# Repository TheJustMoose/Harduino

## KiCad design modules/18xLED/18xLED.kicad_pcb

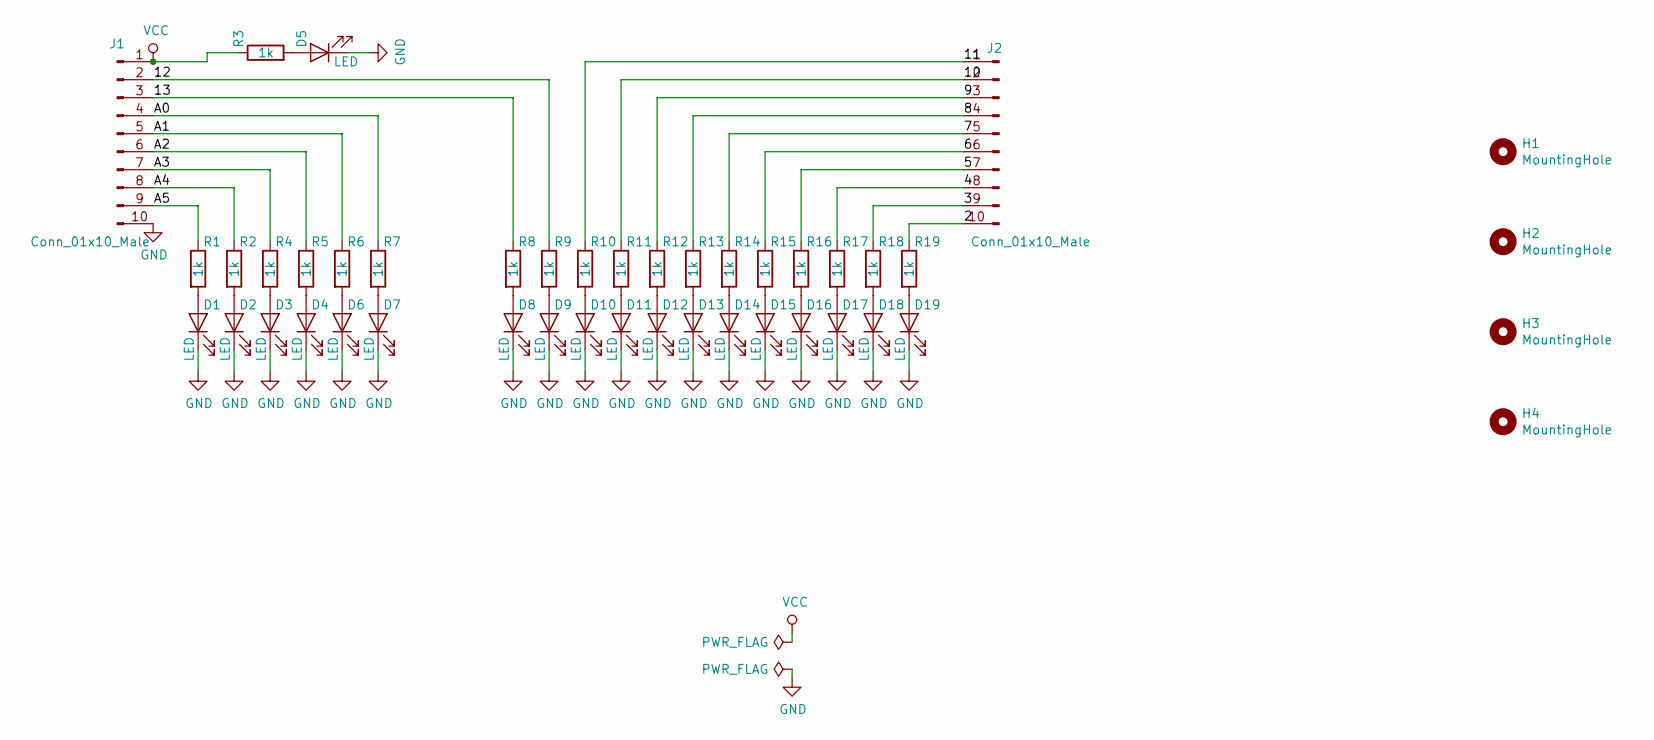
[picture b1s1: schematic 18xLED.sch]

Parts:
D1, D2, D3, D4, D5, D6, D7, D8, D9, D10, D11, D12, D13, D14, D15, D16, D17, D18, D19: LED; LED_0805_2012Metric_Pad1.15x1.40mm_HandSolder
H1, H2, H3, H4: MountingHole; MountingHole_3.2mm_M3
J1, J2: Conn_01x10_Male; PinSocket_1x10_P2.54mm_Vertical
R1, R2, R3, R4, R5, R6, R7, R8, R9, R10, R11, R12, R13, R14, R15, R16, R17, R18, R19: 1k; R_0805_2012Metric_Pad1.15x1.40mm_HandSolder

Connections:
/2: J2.10, R19.1
/3: J2.9, R18.1
/4: J2.8, R17.1
/5: J2.7, R16.1
/6: J2.6, R15.1
/7: J2.5, R14.1
/8: J2.4, R13.1
/9: J2.3, R12.1
/10: J2.2, R11.1
/11: J2.1, R10.1
/12: J1.2, R9.1
/13: J1.3, R8.1
/A0: J1.4, R7.1
/A1: J1.5, R6.1
/A2: J1.6, R5.1
/A3: J1.7, R4.1
/A4: J1.8, R2.1
/A5: J1.9, R1.1
GND: D1.1 (K), D2.1 (K), D3.1 (K), D4.1 (K), D5.1 (K), D6.1 (K), D7.1 (K), D8.1 (K), D9.1 (K), D10.1 (K), D11.1 (K), D12.1 (K), D13.1 (K), D14.1 (K), D15.1 (K), D16.1 (K), D17.1 (K), D18.1 (K), D19.1 (K), J1.10
unnamed: D1.2 (A), R1.2
unnamed: D2.2 (A), R2.2
unnamed: D3.2 (A), R4.2
unnamed: D4.2 (A), R5.2
unnamed: D5.2 (A), R3.2
unnamed: D6.2 (A), R6.2
unnamed: D7.2 (A), R7.2
unnamed: D8.2 (A), R8.2
unnamed: D9.2 (A), R9.2
unnamed: D10.2 (A), R10.2
unnamed: D11.2 (A), R11.2
unnamed: D12.2 (A), R12.2
unnamed: D13.2 (A), R13.2
unnamed: D14.2 (A), R14.2
unnamed: D15.2 (A), R15.2
unnamed: D16.2 (A), R16.2
unnamed: D17.2 (A), R17.2
unnamed: D18.2 (A), R18.2
unnamed: D19.2 (A), R19.2
VCC: J1.1, R3.1

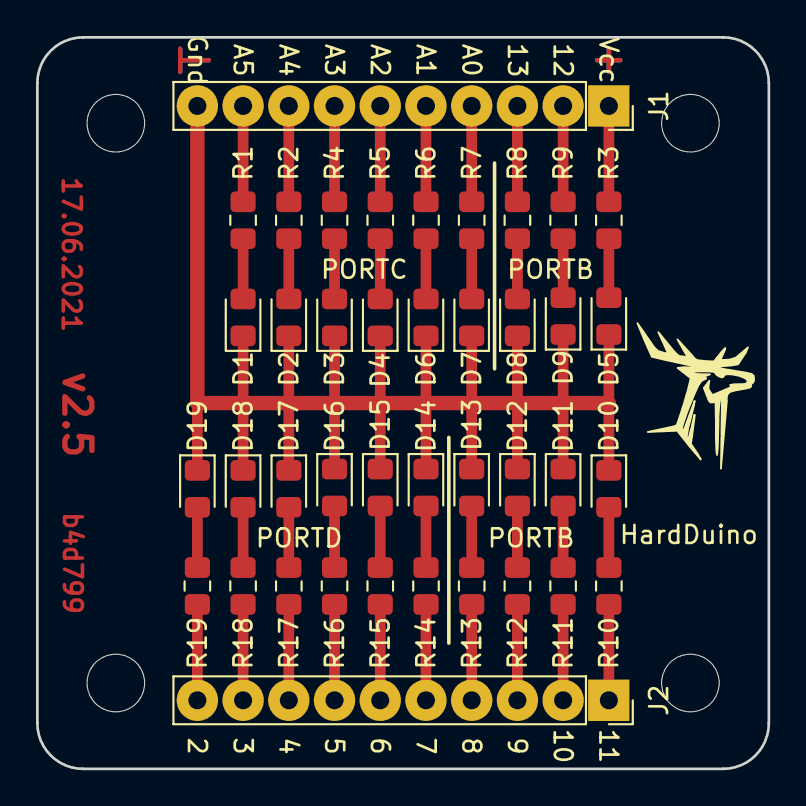
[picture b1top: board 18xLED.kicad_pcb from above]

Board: 2 copper layers, 40.6 x 40.6 mm, 44 parts (0 on the bottom side), 39 nets.

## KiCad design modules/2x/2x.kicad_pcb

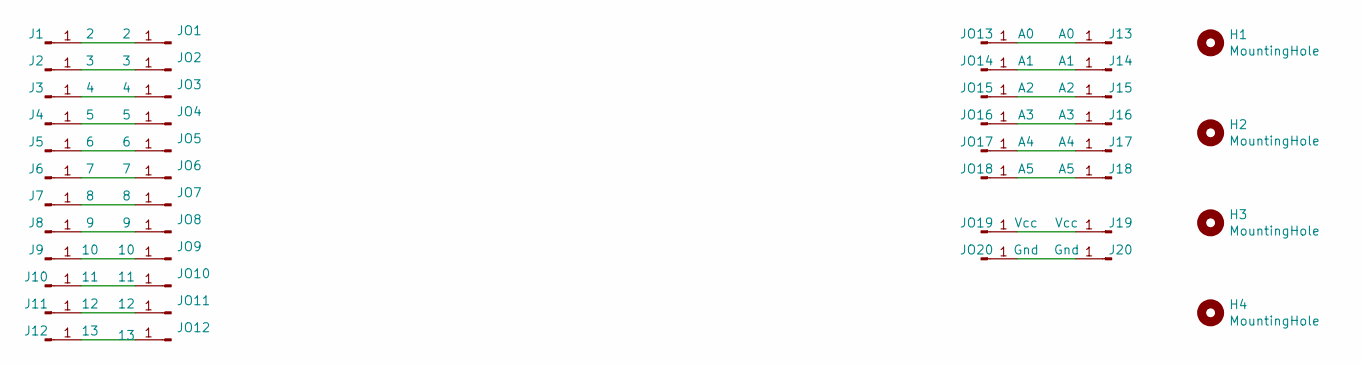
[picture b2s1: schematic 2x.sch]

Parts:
H1, H2, H3, H4: MountingHole; MountingHole_3.2mm_M3
J1: 2; PinHeader_1x01_P2.54mm_Vertical
J2: 3; PinHeader_1x01_P2.54mm_Vertical
J3: 4; PinHeader_1x01_P2.54mm_Vertical
J4: 5; PinHeader_1x01_P2.54mm_Vertical
J5: 6; PinHeader_1x01_P2.54mm_Vertical
J6: 7; PinHeader_1x01_P2.54mm_Vertical
J7: 8; PinHeader_1x01_P2.54mm_Vertical
J8: 9; PinHeader_1x01_P2.54mm_Vertical
J9: 10; PinHeader_1x01_P2.54mm_Vertical
J10: 11; PinHeader_1x01_P2.54mm_Vertical
J11: 12; PinHeader_1x01_P2.54mm_Vertical
J12: 13; PinHeader_1x01_P2.54mm_Vertical
J13: A0; PinHeader_1x01_P2.54mm_Vertical
J14: A1; PinHeader_1x01_P2.54mm_Vertical
J15: A2; PinHeader_1x01_P2.54mm_Vertical
J16: A3; PinHeader_1x01_P2.54mm_Vertical
J17: A4; PinHeader_1x01_P2.54mm_Vertical
J18: A5; PinHeader_1x01_P2.54mm_Vertical
J19: Vcc; PinHeader_1x01_P2.54mm_Vertical
J20: Gnd; PinHeader_1x01_P2.54mm_Vertical
JO1: 2; PinHeader_1x01_P2.54mm_Vertical
JO2: 3; PinHeader_1x01_P2.54mm_Vertical
JO3: 4; PinHeader_1x01_P2.54mm_Vertical
JO4: 5; PinHeader_1x01_P2.54mm_Vertical
JO5: 6; PinHeader_1x01_P2.54mm_Vertical
JO6: 7; PinHeader_1x01_P2.54mm_Vertical
JO7: 8; PinHeader_1x01_P2.54mm_Vertical
JO8: 9; PinHeader_1x01_P2.54mm_Vertical
JO9: 10; PinHeader_1x01_P2.54mm_Vertical
JO10: 11; PinHeader_1x01_P2.54mm_Vertical
JO11: 12; PinHeader_1x01_P2.54mm_Vertical
JO12: 13; PinHeader_1x01_P2.54mm_Vertical
JO13: A0; PinHeader_1x01_P2.54mm_Vertical
JO14: A1; PinHeader_1x01_P2.54mm_Vertical
JO15: A2; PinHeader_1x01_P2.54mm_Vertical
JO16: A3; PinHeader_1x01_P2.54mm_Vertical
JO17: A4; PinHeader_1x01_P2.54mm_Vertical
JO18: A5; PinHeader_1x01_P2.54mm_Vertical
JO19: Vcc; PinHeader_1x01_P2.54mm_Vertical
JO20: Gnd; PinHeader_1x01_P2.54mm_Vertical

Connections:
unnamed: J1.1, JO1.1
unnamed: J2.1, JO2.1
unnamed: J3.1, JO3.1
unnamed: J4.1, JO4.1
unnamed: J5.1, JO5.1
unnamed: J6.1, JO6.1
unnamed: J7.1, JO7.1
unnamed: J8.1, JO8.1
unnamed: J9.1, JO9.1
unnamed: J10.1, JO10.1
unnamed: J11.1, JO11.1
unnamed: J12.1, JO12.1
unnamed: J13.1, JO13.1
unnamed: J14.1, JO14.1
unnamed: J15.1, JO15.1
unnamed: J16.1, JO16.1
unnamed: J17.1, JO17.1
unnamed: J18.1, JO18.1
unnamed: J19.1, JO19.1
unnamed: J20.1, JO20.1

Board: 2 copper layers, 48 parts (0 on the bottom side), 20 nets, no tracks yet.

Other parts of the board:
H3#2, H3#3, H4#2, H4#3: MountingHole; MountingHole_3.2mm_M3

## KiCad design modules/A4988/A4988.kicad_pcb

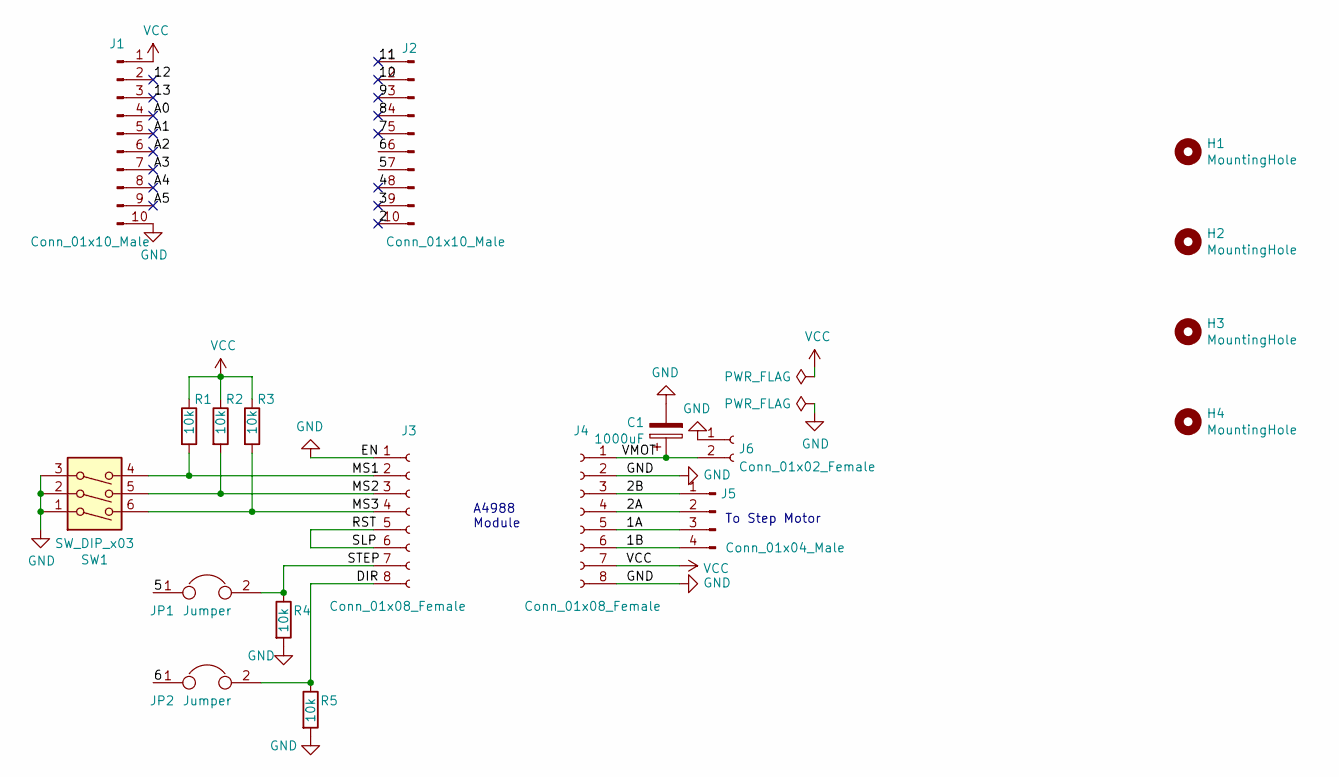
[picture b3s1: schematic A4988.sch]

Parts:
C1: 1000uF; CP_Radial_D13.0mm_P5.00mm
H1, H2, H3, H4: MountingHole; MountingHole_3.2mm_M3
J1, J2: Conn_01x10_Male; PinSocket_1x10_P2.54mm_Vertical
J3, J4: Conn_01x08_Female; PinSocket_1x08_P2.54mm_Vertical
J5: Conn_01x04_Male; JST_XH_B4B-XH-A_1x04_P2.50mm_Vertical
J6: Conn_01x02_Female; TerminalBlock_bornier-2_P5.08mm
JP1, JP2: Jumper; PinHeader_1x02_P2.54mm_Vertical
R1, R2, R3, R4, R5: 10k; R_0805_2012Metric_Pad1.20x1.40mm_HandSolder
SW1: SW_DIP_x03; SW_DIP_SPSTx03_Slide_9.78x9.8mm_W7.62mm_P2.54mm

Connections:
/1A: J4.5, J5.3
/1B: J4.6, J5.4
/2: J2.10
/2A: J4.4, J5.2
/2B: J4.3, J5.1
/3: J2.9
/4: J2.8
/5: J2.7, JP1.1
/6: J2.6, JP2.1
/7: J2.5
/8: J2.4
/9: J2.3
/10: J2.2
/11: J2.1
/12: J1.2
/13: J1.3
/A0: J1.4
/A1: J1.5
/A2: J1.6
/A3: J1.7
/A4: J1.8
/A5: J1.9
/DIR: J3.8, JP2.2, R5.1
/MS1: J3.2, R1.2, SW1.4
/MS2: J3.3, R2.2, SW1.5
/MS3: J3.4, R3.2, SW1.6
/RST: J3.5, J3.6
/STEP: J3.7, JP1.2, R4.1
/VMOT: C1.1, J4.1, J6.2
GND: C1.2, J1.10, J3.1, J4.2, J4.8, J6.1, R4.2, R5.2, SW1.1, SW1.2, SW1.3
VCC: J1.1, J4.7, R1.1, R2.1, R3.1

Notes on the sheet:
A4988 Module
To Step Motor

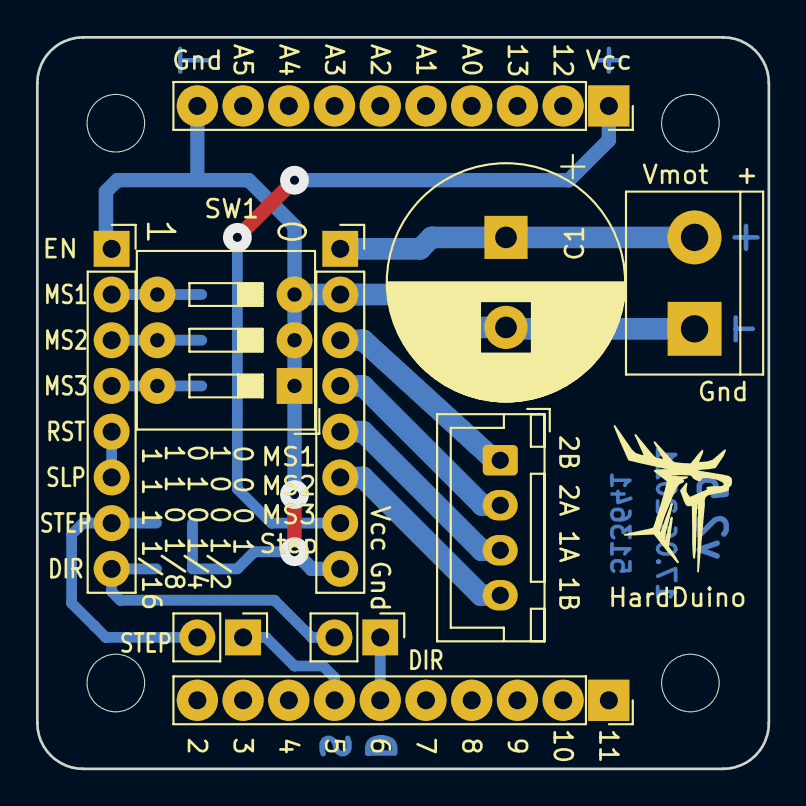
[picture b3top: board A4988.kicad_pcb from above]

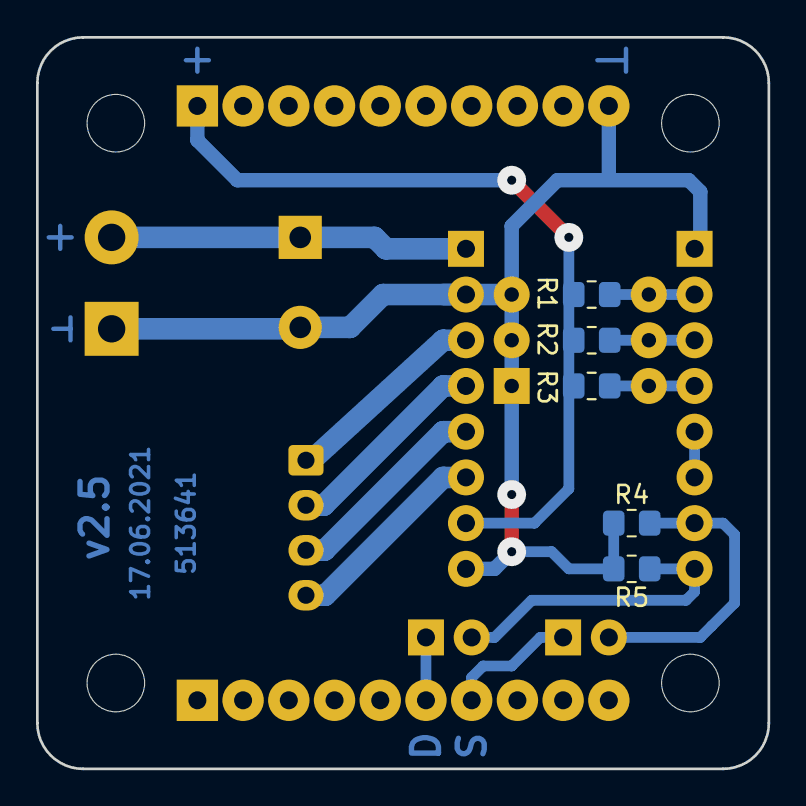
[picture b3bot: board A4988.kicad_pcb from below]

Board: 2 copper layers, 40.6 x 40.6 mm, 19 parts (5 on the bottom side), 15 nets.

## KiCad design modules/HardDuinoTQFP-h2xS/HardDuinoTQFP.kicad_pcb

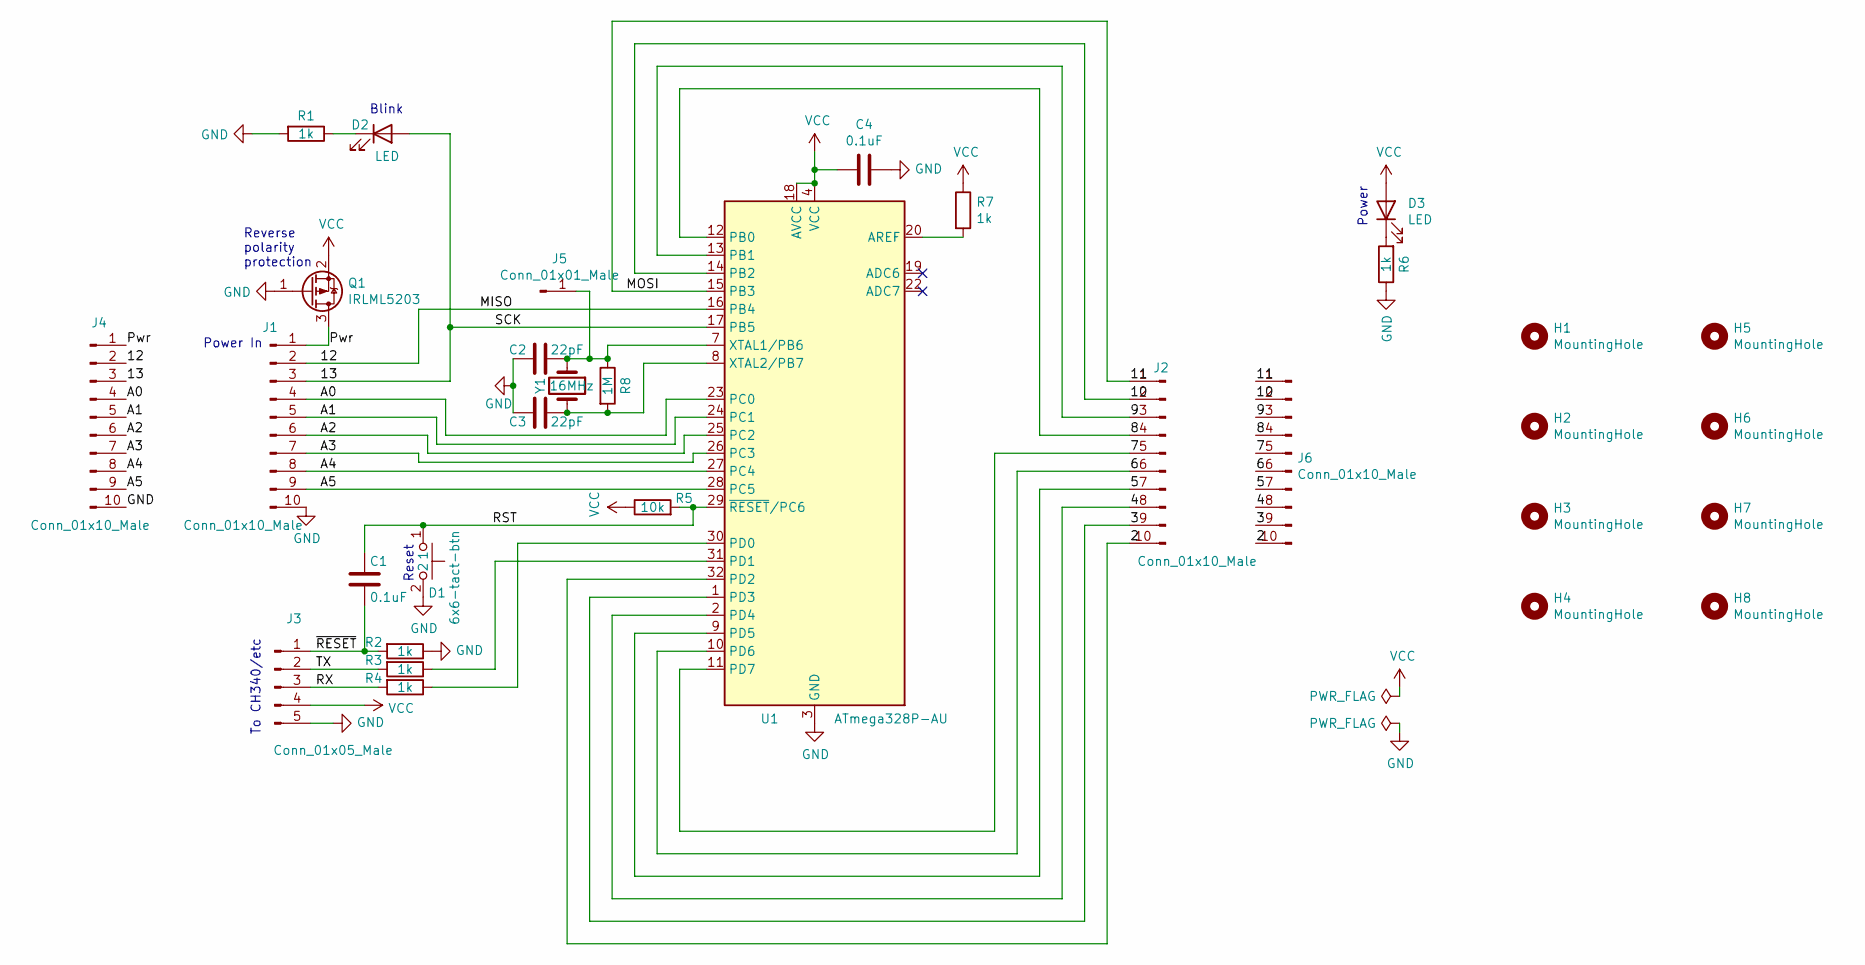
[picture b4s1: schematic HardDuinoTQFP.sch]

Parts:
C1, C4: 0.1uF; C_0805_2012Metric_Pad1.15x1.40mm_HandSolder
C2, C3: 22pF; C_0805_2012Metric_Pad1.15x1.40mm_HandSolder
D1: 6x6-tact-btn
D2, D3: LED; LED_0805_2012Metric_Pad1.15x1.40mm_HandSolder
H1, H2, H3, H4, H5, H6, H7, H8: MountingHole; MountingHole_3.2mm_M3
J1, J2, J4, J6: Conn_01x10_Male; PinSocket_1x10_P2.54mm_Vertical
J3: Conn_01x05_Male; PinHeader_1x05_P2.54mm_Vertical
J5: Conn_01x01_Male; PinHeader_1x01_P2.54mm_Vertical
Q1: IRLML5203; SOT-23
R1, R2, R3, R4, R6, R7: 1k; R_0805_2012Metric_Pad1.15x1.40mm_HandSolder
R5: 10k; R_0805_2012Metric_Pad1.15x1.40mm_HandSolder
R8: 1M; R_0805_2012Metric_Pad1.15x1.40mm_HandSolder
U1: ATmega328P-AU; TQFP-32_7x7mm_P0.8mm
Y1: 16MHz; Crystal_HC49-U_Vertical

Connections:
/2: J2.10, J6.10, U1.32 (PD2)
/3: J2.9, J6.9, U1.1 (PD3)
/4: J2.8, J6.8, U1.2 (PD4)
/5: J2.7, J6.7, U1.9 (PD5)
/6: J2.6, J6.6, U1.10 (PD6)
/7: J2.5, J6.5, U1.11 (PD7)
/8: J2.4, J6.4, U1.12 (PB0)
/9: J2.3, J6.3, U1.13 (PB1)
/10: J2.2, J6.2, U1.14 (PB2)
/11: J2.1, J6.1, U1.15 (PB3)
/12: J1.2, J4.2, U1.16 (PB4)
/13: D2.2 (A), J1.3, J4.3, U1.17 (PB5)
/A0: J1.4, J4.4, U1.23 (PC0)
/A1: J1.5, J4.5, U1.24 (PC1)
/A2: J1.6, J4.6, U1.25 (PC2)
/A3: J1.7, J4.7, U1.26 (PC3)
/A4: J1.8, J4.8, U1.27 (PC4)
/A5: J1.9, J4.9, U1.28 (PC5)
/Pwr: J1.1, J4.1, Q1.3 (D)
/RST: C1.1, D1.1, R5.2, U1.29 (~RESET~/PC6)
/RX: J3.3, R4.2
/TX: J3.2, R3.2
/~RESET: C1.2, J3.1, R2.2
GND: C2.2, C3.1, C4.1, D1.2, J1.10, J3.5, J4.10, Q1.1 (G), R1.2, R2.1, R6.1, U1.3 (GND), U1.5 (GND), U1.21 (GND)
unnamed: C2.1, J5.1, R8.1, U1.7 (XTAL1/PB6), Y1.1
unnamed: C3.2, R8.2, U1.8 (XTAL2/PB7), Y1.2
unnamed: D2.1 (K), R1.1
unnamed: D3.1 (K), R6.2
unnamed: R3.1, U1.31 (PD1)
unnamed: R4.1, U1.30 (PD0)
unnamed: R7.2, U1.20 (AREF)
VCC: C4.2, D3.2 (A), J3.4, Q1.2 (S), R5.1, R7.1, U1.4 (VCC), U1.6 (VCC), U1.18 (AVCC)

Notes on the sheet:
Power In
Reverse polarity protection
Blink
Power
Reset
To CH340/etc

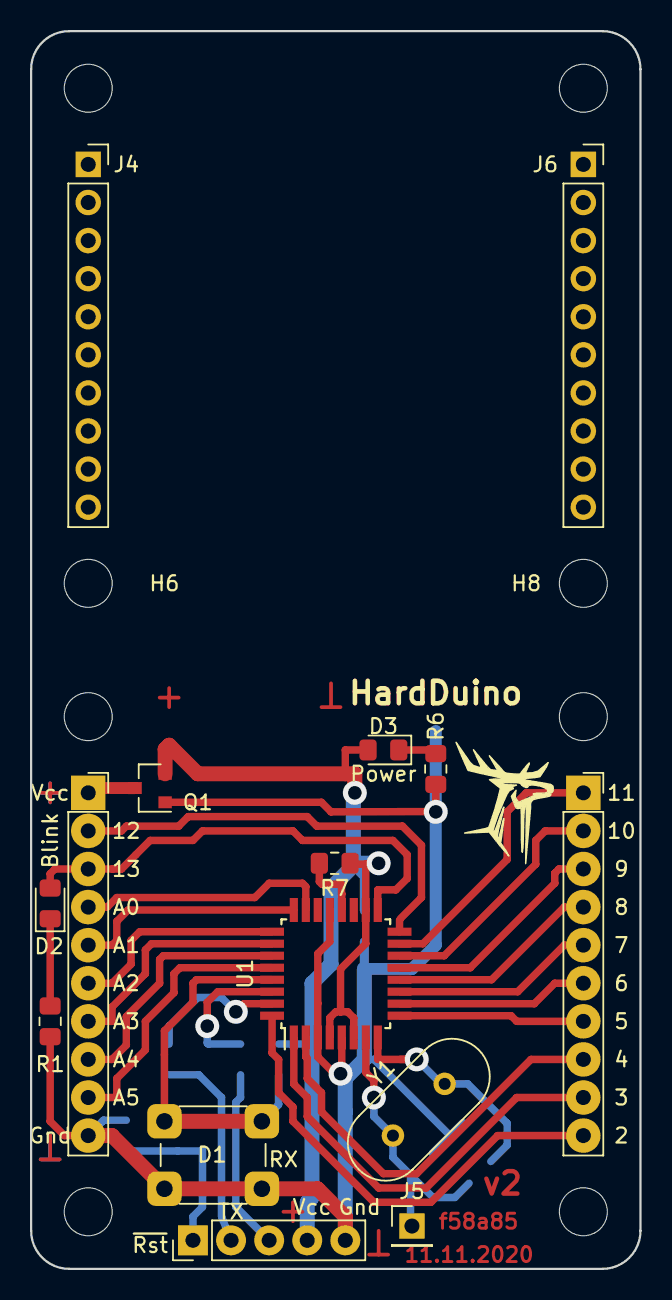
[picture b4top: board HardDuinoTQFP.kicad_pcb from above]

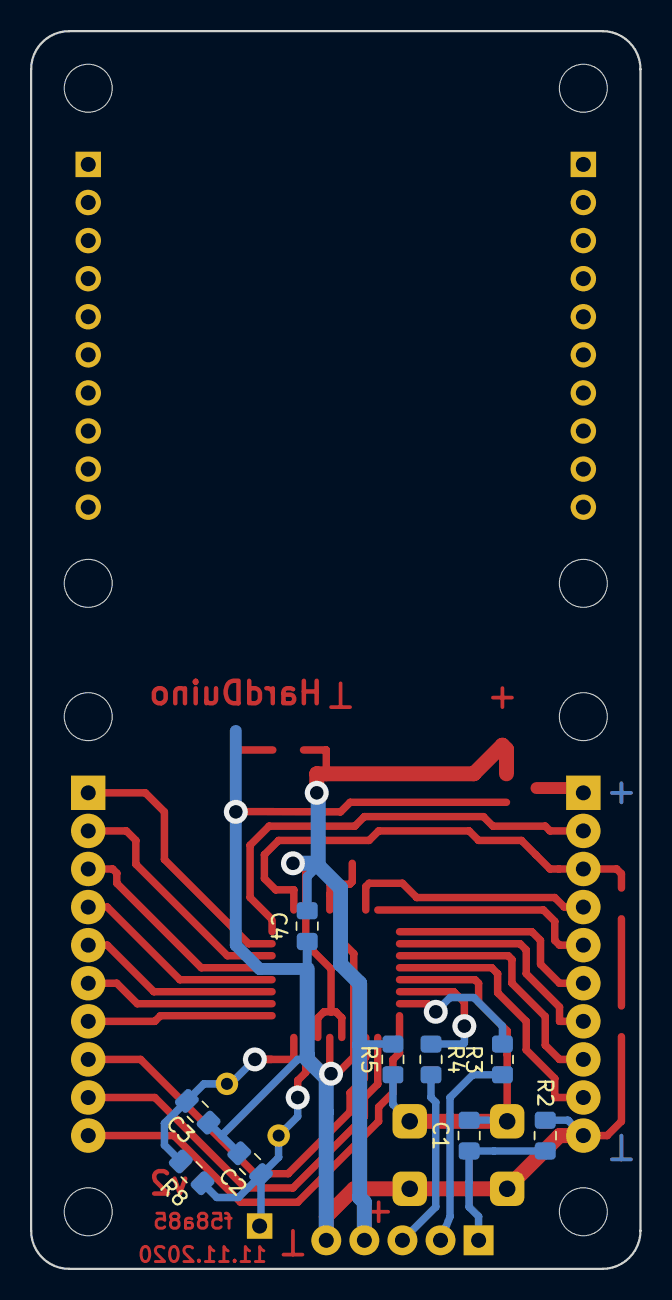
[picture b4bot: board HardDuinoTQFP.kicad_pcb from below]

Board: 2 copper layers, 40.6 x 82.6 mm, 32 parts (9 on the bottom side), 32 nets.

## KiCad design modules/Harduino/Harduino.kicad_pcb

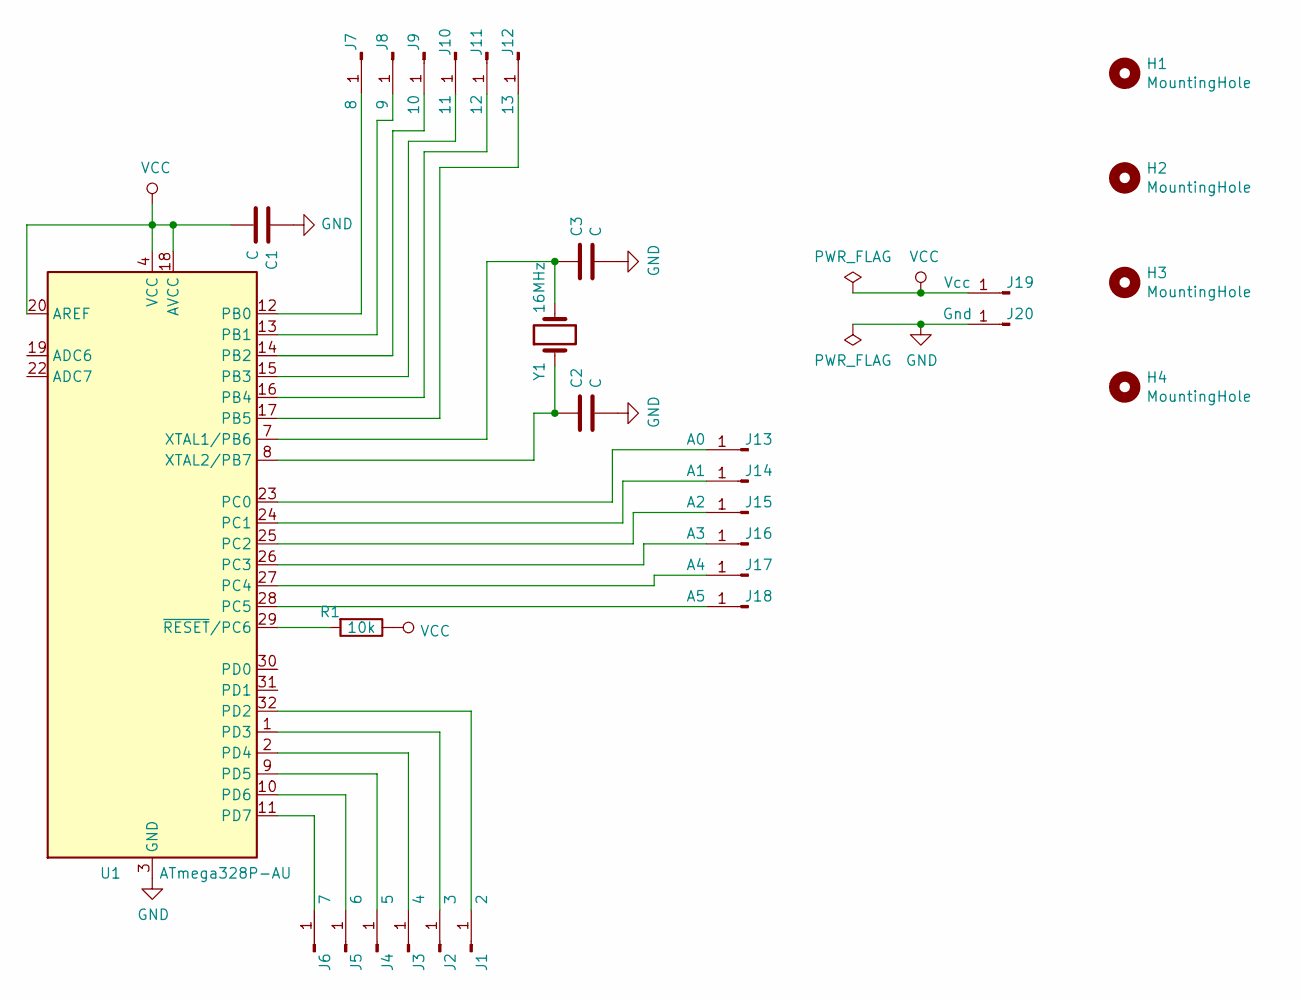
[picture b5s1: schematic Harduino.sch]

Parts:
C1, C2, C3: C; C_0805_2012Metric_Pad1.15x1.40mm_HandSolder
H1, H2, H3, H4: MountingHole; MountingHole_3.2mm_M3
J1: 2; PinHeader_1x01_P2.54mm_Vertical
J2: 3; PinHeader_1x01_P2.54mm_Vertical
J3: 4; PinHeader_1x01_P2.54mm_Vertical
J4: 5; PinHeader_1x01_P2.54mm_Vertical
J5: 6; PinHeader_1x01_P2.54mm_Vertical
J6: 7; PinHeader_1x01_P2.54mm_Vertical
J7: 8; PinHeader_1x01_P2.54mm_Vertical
J8: 9; PinHeader_1x01_P2.54mm_Vertical
J9: 10; PinHeader_1x01_P2.54mm_Vertical
J10: 11; PinHeader_1x01_P2.54mm_Vertical
J11: 12; PinHeader_1x01_P2.54mm_Vertical
J12: 13; PinHeader_1x01_P2.54mm_Vertical
J13: A0; PinHeader_1x01_P2.54mm_Vertical
J14: A1; PinHeader_1x01_P2.54mm_Vertical
J15: A2; PinHeader_1x01_P2.54mm_Vertical
J16: A3; PinHeader_1x01_P2.54mm_Vertical
J17: A4; PinHeader_1x01_P2.54mm_Vertical
J18: A5; PinHeader_1x01_P2.54mm_Vertical
J19: Vcc; PinHeader_1x01_P2.54mm_Vertical
J20: Gnd; PinHeader_1x01_P2.54mm_Vertical
R1: 10k; R_0805_2012Metric_Pad1.15x1.40mm_HandSolder
U1: ATmega328P-AU; TQFP-32_7x7mm_P0.8mm
Y1: 16MHz; Crystal_SMD_HC49-SD_HandSoldering

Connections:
GND: C1.1, C2.2, C3.2, J20.1, U1.3 (GND), U1.5 (GND), U1.21 (GND)
unnamed: C2.1, U1.8 (XTAL2/PB7), Y1.1
unnamed: C3.1, U1.7 (XTAL1/PB6), Y1.2
unnamed: J1.1, U1.32 (PD2)
unnamed: J2.1, U1.1 (PD3)
unnamed: J3.1, U1.2 (PD4)
unnamed: J4.1, U1.9 (PD5)
unnamed: J5.1, U1.10 (PD6)
unnamed: J6.1, U1.11 (PD7)
unnamed: J7.1, U1.12 (PB0)
unnamed: J8.1, U1.13 (PB1)
unnamed: J9.1, U1.14 (PB2)
unnamed: J10.1, U1.15 (PB3)
unnamed: J11.1, U1.16 (PB4)
unnamed: J12.1, U1.17 (PB5)
unnamed: J13.1, U1.23 (PC0)
unnamed: J14.1, U1.24 (PC1)
unnamed: J15.1, U1.25 (PC2)
unnamed: J16.1, U1.26 (PC3)
unnamed: J17.1, U1.27 (PC4)
unnamed: J18.1, U1.28 (PC5)
unnamed: R1.2, U1.29 (~RESET~/PC6)
VCC: C1.2, J19.1, R1.1, U1.4 (VCC), U1.6 (VCC), U1.18 (AVCC), U1.20 (AREF)

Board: 2 copper layers, 30 parts (0 on the bottom side), 23 nets, no tracks yet.

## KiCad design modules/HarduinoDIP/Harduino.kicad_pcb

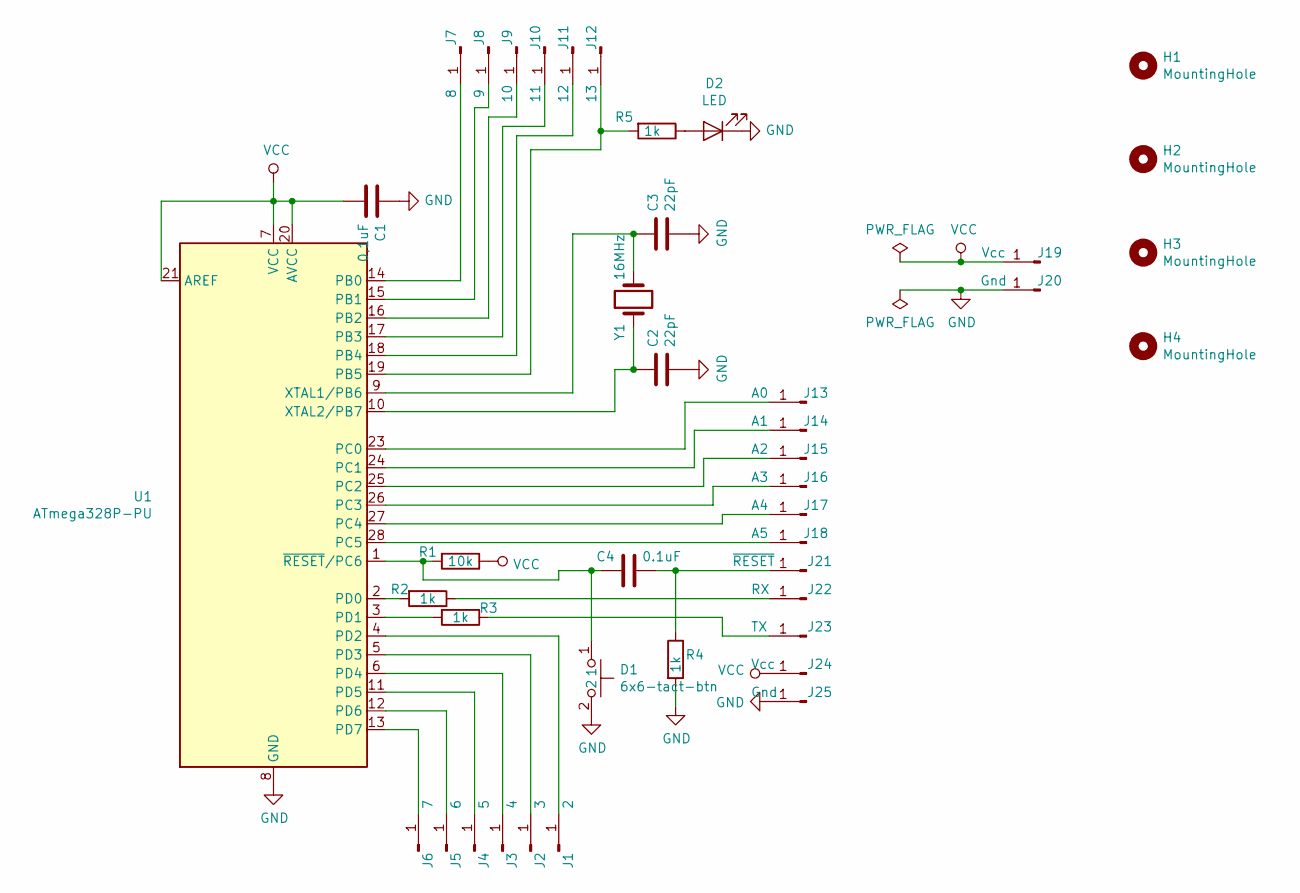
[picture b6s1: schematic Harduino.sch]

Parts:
C1: 0,1uF; C_0805_2012Metric_Pad1.15x1.40mm_HandSolder
C2, C3: 22pF; C_0805_2012Metric_Pad1.15x1.40mm_HandSolder
C4: 0.1uF; C_0805_2012Metric_Pad1.15x1.40mm_HandSolder
D1: 6x6-tact-btn
D2: LED; LED_0805_2012Metric_Pad1.15x1.40mm_HandSolder
H1, H2, H3, H4: MountingHole; MountingHole_3.2mm_M3
J1: 2; PinHeader_1x01_P2.54mm_Vertical
J2: 3; PinHeader_1x01_P2.54mm_Vertical
J3: 4; PinHeader_1x01_P2.54mm_Vertical
J4: 5; PinHeader_1x01_P2.54mm_Vertical
J5: 6; PinHeader_1x01_P2.54mm_Vertical
J6: 7; PinHeader_1x01_P2.54mm_Vertical
J7: 8; PinHeader_1x01_P2.54mm_Vertical
J8: 9; PinHeader_1x01_P2.54mm_Vertical
J9: 10; PinHeader_1x01_P2.54mm_Vertical
J10: 11; PinHeader_1x01_P2.54mm_Vertical
J11: 12; PinHeader_1x01_P2.54mm_Vertical
J12: 13; PinHeader_1x01_P2.54mm_Vertical
J13: A0; PinHeader_1x01_P2.54mm_Vertical
J14: A1; PinHeader_1x01_P2.54mm_Vertical
J15: A2; PinHeader_1x01_P2.54mm_Vertical
J16: A3; PinHeader_1x01_P2.54mm_Vertical
J17: A4; PinHeader_1x01_P2.54mm_Vertical
J18: A5; PinHeader_1x01_P2.54mm_Vertical
J19, J24: Vcc; PinHeader_1x01_P2.54mm_Vertical
J20, J25: Gnd; PinHeader_1x01_P2.54mm_Vertical
J21: ~RESET; PinHeader_1x01_P2.54mm_Vertical
J22: RX; PinHeader_1x01_P2.54mm_Vertical
J23: TX; PinHeader_1x01_P2.54mm_Vertical
R1: 10k; R_0805_2012Metric_Pad1.15x1.40mm_HandSolder
R2, R3, R4, R5: 1k; R_0805_2012Metric_Pad1.15x1.40mm_HandSolder
U1: ATmega328P-PU; DIP-28_W7.62mm
Y1: 16MHz; Crystal_HC49-U_Vertical

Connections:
GND: C1.1, C2.2, C3.2, D1.2, D2.1 (K), J20.1, J25.1, R4.2, U1.8 (GND), U1.22 (GND)
unnamed: C2.1, U1.10 (XTAL2/PB7), Y1.1
unnamed: C3.1, U1.9 (XTAL1/PB6), Y1.2
unnamed: C4.1, J21.1, R4.1
unnamed: C4.2, D1.1, R1.2, U1.1 (~RESET~/PC6)
unnamed: D2.2 (A), R5.1
unnamed: J1.1, U1.4 (PD2)
unnamed: J2.1, U1.5 (PD3)
unnamed: J3.1, U1.6 (PD4)
unnamed: J4.1, U1.11 (PD5)
unnamed: J5.1, U1.12 (PD6)
unnamed: J6.1, U1.13 (PD7)
unnamed: J7.1, U1.14 (PB0)
unnamed: J8.1, U1.15 (PB1)
unnamed: J9.1, U1.16 (PB2)
unnamed: J10.1, U1.17 (PB3)
unnamed: J11.1, U1.18 (PB4)
unnamed: J12.1, R5.2, U1.19 (PB5)
unnamed: J13.1, U1.23 (PC0)
unnamed: J14.1, U1.24 (PC1)
unnamed: J15.1, U1.25 (PC2)
unnamed: J16.1, U1.26 (PC3)
unnamed: J17.1, U1.27 (PC4)
unnamed: J18.1, U1.28 (PC5)
unnamed: J22.1, R2.1
unnamed: J23.1, R3.1
unnamed: R2.2, U1.2 (PD0)
unnamed: R3.2, U1.3 (PD1)
VCC: C1.2, J19.1, J24.1, R1.1, U1.7 (VCC), U1.20 (AVCC), U1.21 (AREF)

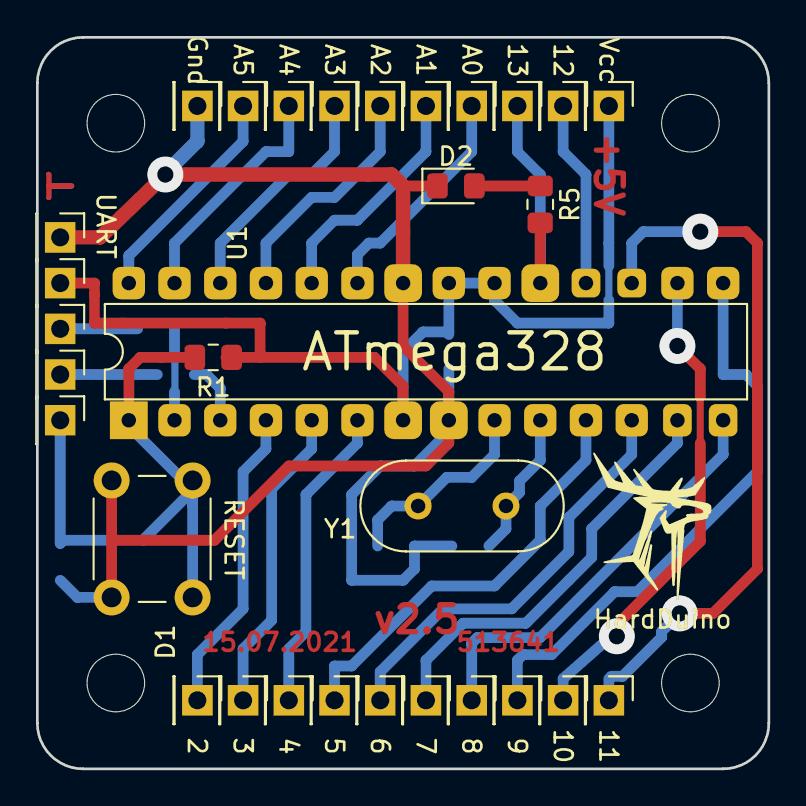
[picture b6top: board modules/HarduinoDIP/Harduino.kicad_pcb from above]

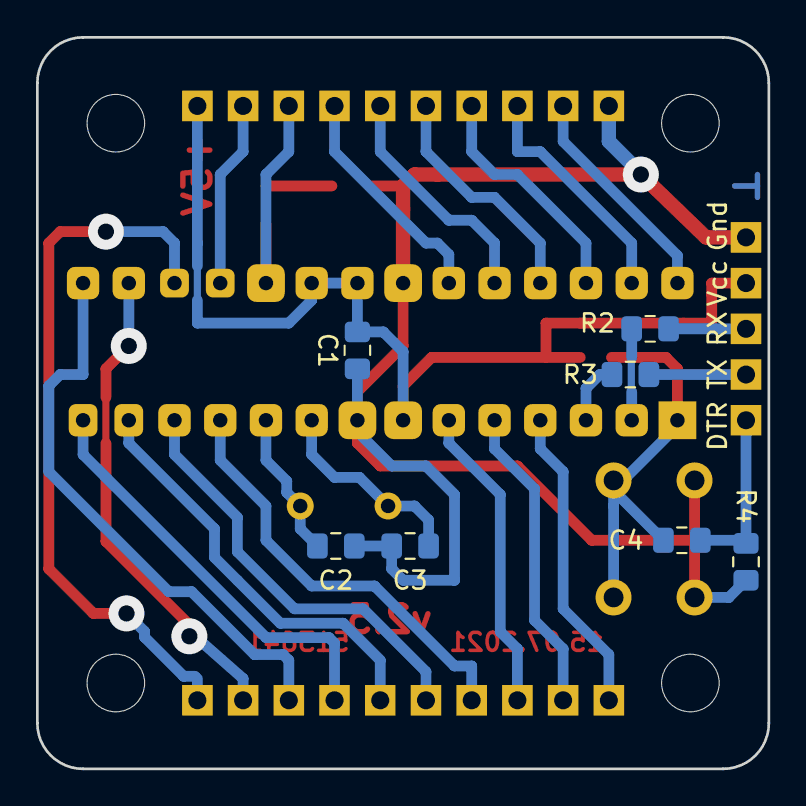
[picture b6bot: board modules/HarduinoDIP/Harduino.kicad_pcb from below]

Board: 2 copper layers, 40.6 x 40.6 mm, 42 parts (7 on the bottom side), 29 nets.

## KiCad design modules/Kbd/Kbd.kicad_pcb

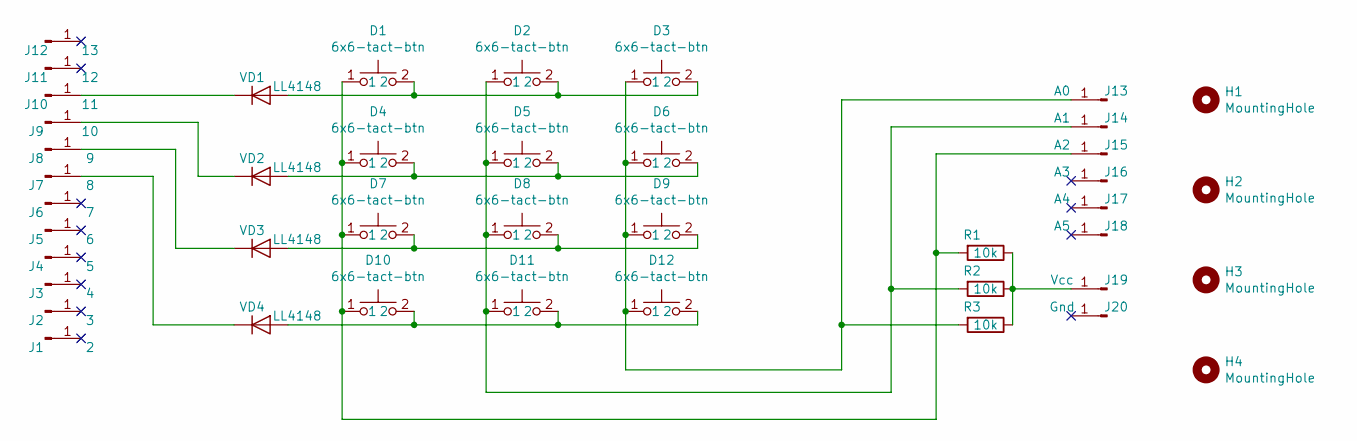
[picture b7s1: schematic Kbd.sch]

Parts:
D1, D2, D3, D4, D5, D6, D7, D8, D9, D10, D11, D12: 6x6-tact-btn
H1, H2, H3, H4: MountingHole; MountingHole_3.2mm_M3
J1: 2; PinHeader_1x01_P2.54mm_Vertical
J2: 3; PinHeader_1x01_P2.54mm_Vertical
J3: 4; PinHeader_1x01_P2.54mm_Vertical
J4: 5; PinHeader_1x01_P2.54mm_Vertical
J5: 6; PinHeader_1x01_P2.54mm_Vertical
J6: 7; PinHeader_1x01_P2.54mm_Vertical
J7: 8; PinHeader_1x01_P2.54mm_Vertical
J8: 9; PinHeader_1x01_P2.54mm_Vertical
J9: 10; PinHeader_1x01_P2.54mm_Vertical
J10: 11; PinHeader_1x01_P2.54mm_Vertical
J11: 12; PinHeader_1x01_P2.54mm_Vertical
J12: 13; PinHeader_1x01_P2.54mm_Vertical
J13: A0; PinHeader_1x01_P2.54mm_Vertical
J14: A1; PinHeader_1x01_P2.54mm_Vertical
J15: A2; PinHeader_1x01_P2.54mm_Vertical
J16: A3; PinHeader_1x01_P2.54mm_Vertical
J17: A4; PinHeader_1x01_P2.54mm_Vertical
J18: A5; PinHeader_1x01_P2.54mm_Vertical
J19: Vcc; PinHeader_1x01_P2.54mm_Vertical
J20: Gnd; PinHeader_1x01_P2.54mm_Vertical
R1, R2, R3: 10k; R_0805_2012Metric_Pad1.15x1.40mm_HandSolder
VD1, VD2, VD3, VD4: LL4148; D_MiniMELF

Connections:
unnamed: D1.1, D4.1, D7.1, D10.1, J15.1, R1.2
unnamed: D1.2, D2.2, D3.2, VD1.2 (A)
unnamed: D4.2, D5.2, D6.2, VD2.2 (A)
unnamed: D7.2, D8.2, D9.2, VD3.2 (A)
unnamed: D10.2, D11.2, D12.2, VD4.2 (A)
unnamed: D2.1, D5.1, D8.1, D11.1, J14.1, R2.2
unnamed: D3.1, D6.1, D9.1, D12.1, J13.1, R3.2
unnamed: J7.1, VD4.1 (K)
unnamed: J8.1, VD3.1 (K)
unnamed: J9.1, VD2.1 (K)
unnamed: J10.1, VD1.1 (K)
unnamed: J19.1, R1.1, R2.1, R3.1

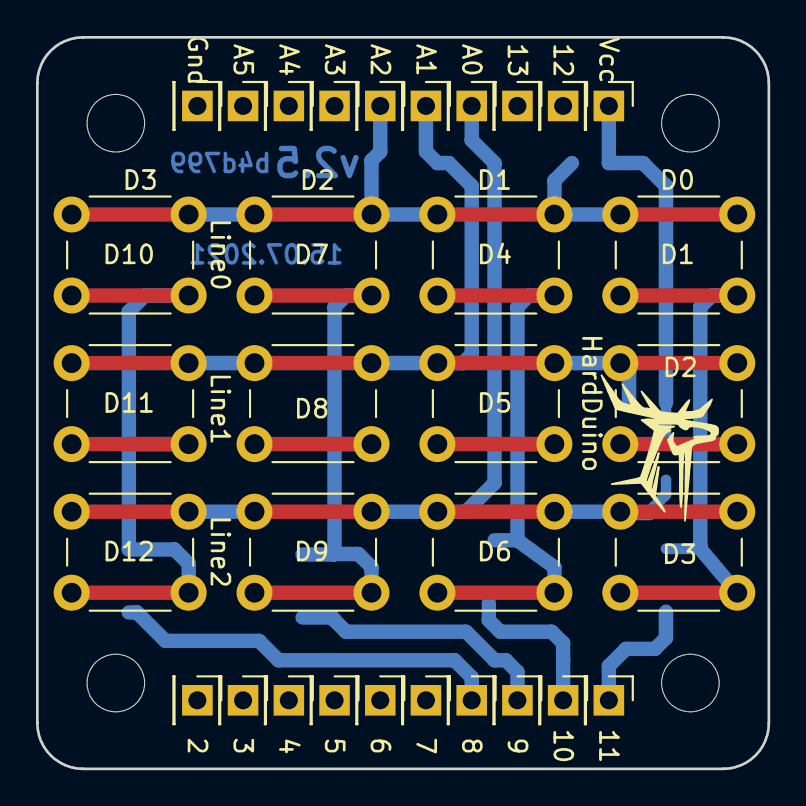
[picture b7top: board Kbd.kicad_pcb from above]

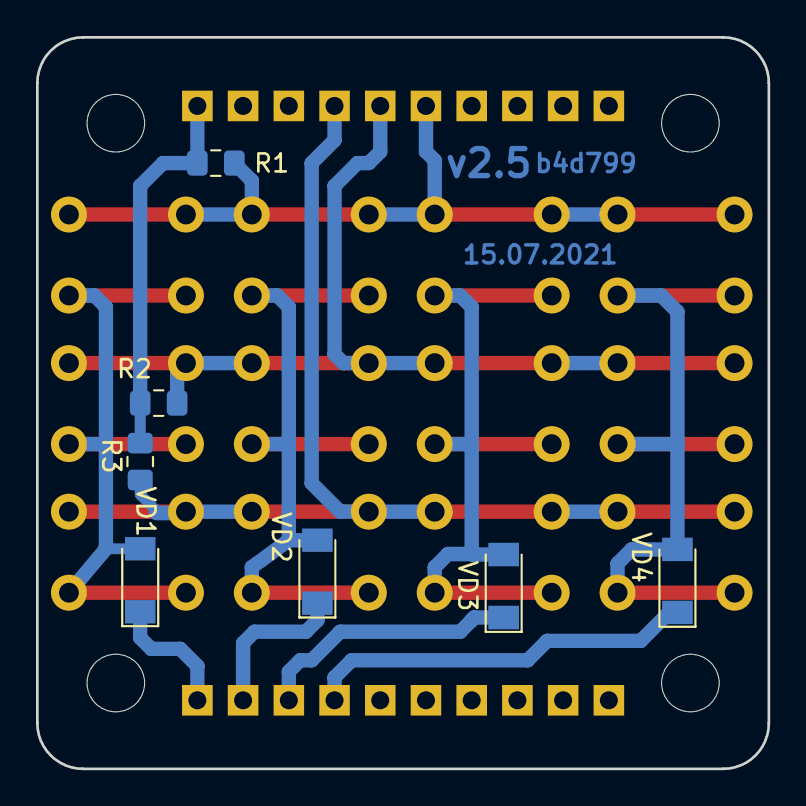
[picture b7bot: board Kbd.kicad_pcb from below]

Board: 2 copper layers, 40.6 x 40.6 mm, 43 parts (7 on the bottom side), 12 nets.
